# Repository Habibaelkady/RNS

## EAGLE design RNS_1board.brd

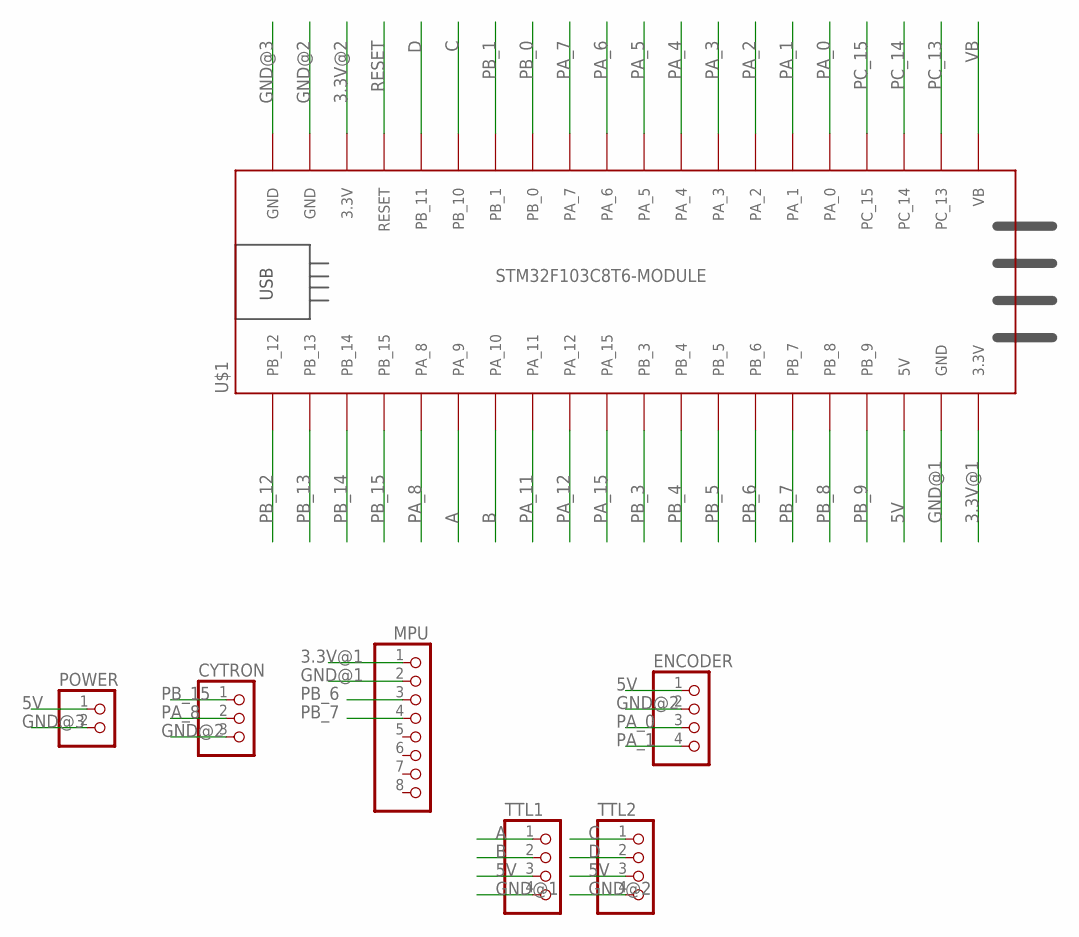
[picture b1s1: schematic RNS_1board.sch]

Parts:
CYTRON: PINHD-3_DATA; 1X03_DATA
ENCODER: PINHD-4_DATA; 1X04_DATA
MPU: PINHD-8_DATA; 1X08_DATA
POWER: PINHD-2_DATA; 1X02_DATA
TTL1, TTL2: PINHD-4_DATA; 1X04_DATA
U$1: STM32F103C8T6-MODULE

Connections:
3.3V@1: MPU.1, U$1.3.3V_1 (3.3V)
3.3V@2: U$1.3.3V_2 (3.3V)
5V: ENCODER.1, POWER.1, TTL1.3, TTL2.3, U$1.5V
A: TTL1.1, U$1.PA_9
B: TTL1.2, U$1.PA_10
C: TTL2.1, U$1.PB_10
D: TTL2.2, U$1.PB_11
GND@1: MPU.2, TTL1.4, U$1.GND_1 (GND)
GND@2: CYTRON.3, ENCODER.2, TTL2.4, U$1.GND_2 (GND)
GND@3: POWER.2, U$1.GND_3 (GND)
PA_0: ENCODER.3, U$1.PA_0
PA_1: ENCODER.4, U$1.PA_1
PA_2: U$1.PA_2
PA_3: U$1.PA_3
PA_4: U$1.PA_4
PA_5: U$1.PA_5
PA_6: U$1.PA_6
PA_7: U$1.PA_7
PA_8: CYTRON.2, U$1.PA_8
PA_11: U$1.PA_11
PA_12: U$1.PA_12
PA_15: U$1.PA_15
PB_0: U$1.PB_0
PB_1: U$1.PB_1
PB_3: U$1.PB_3
PB_4: U$1.PB_4
PB_5: U$1.PB_5
PB_6: MPU.3, U$1.PB_6
PB_7: MPU.4, U$1.PB_7
PB_8: U$1.PB_8
PB_9: U$1.PB_9
PB_12: U$1.PB_12
PB_13: U$1.PB_13
PB_14: U$1.PB_14
PB_15: CYTRON.1, U$1.PB_15
PC_13: U$1.PC_13
PC_14: U$1.PC_14
PC_15: U$1.PC_15
RESET: U$1.RESET
VB: U$1.VB

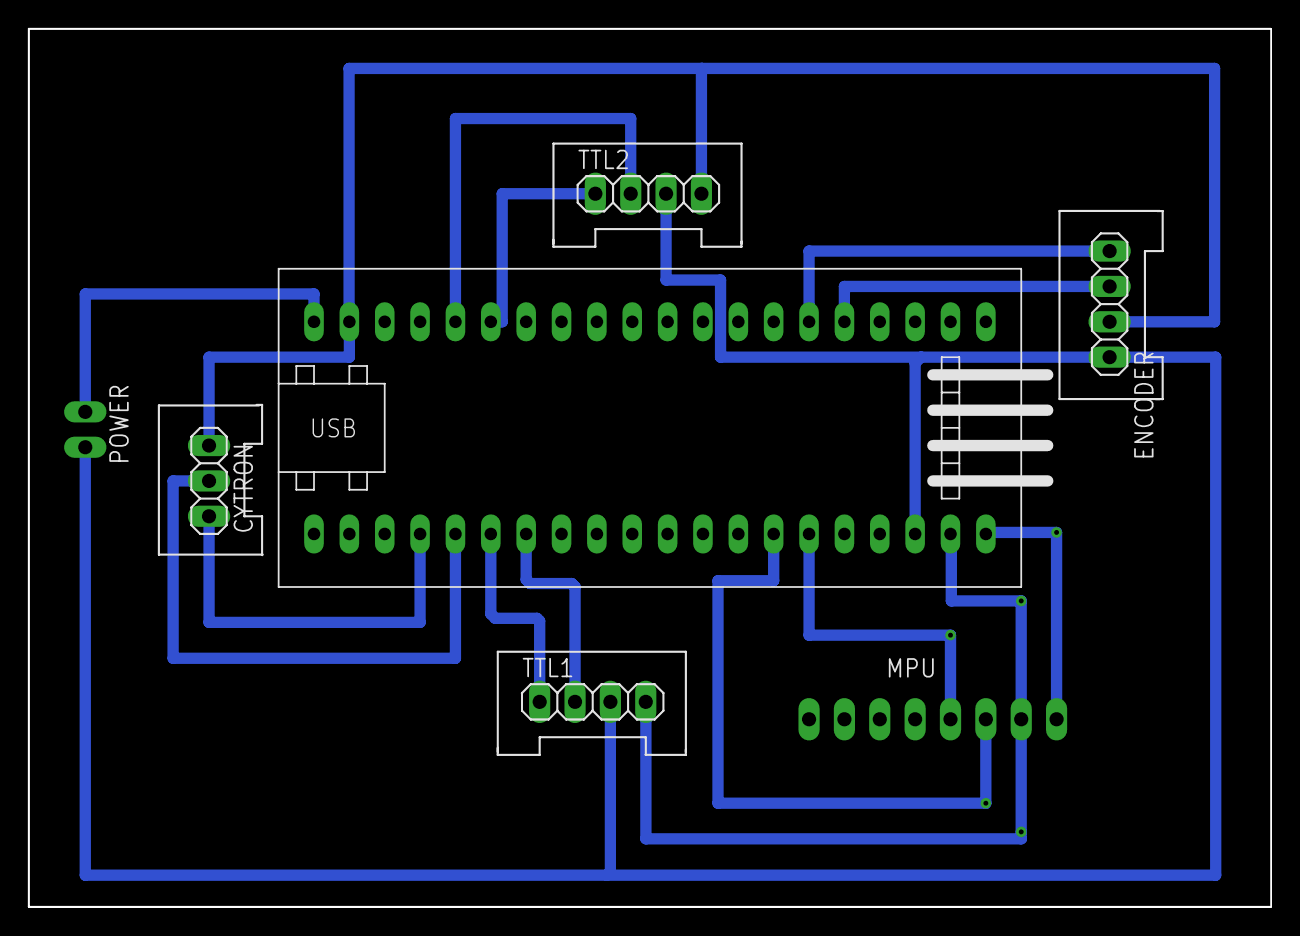
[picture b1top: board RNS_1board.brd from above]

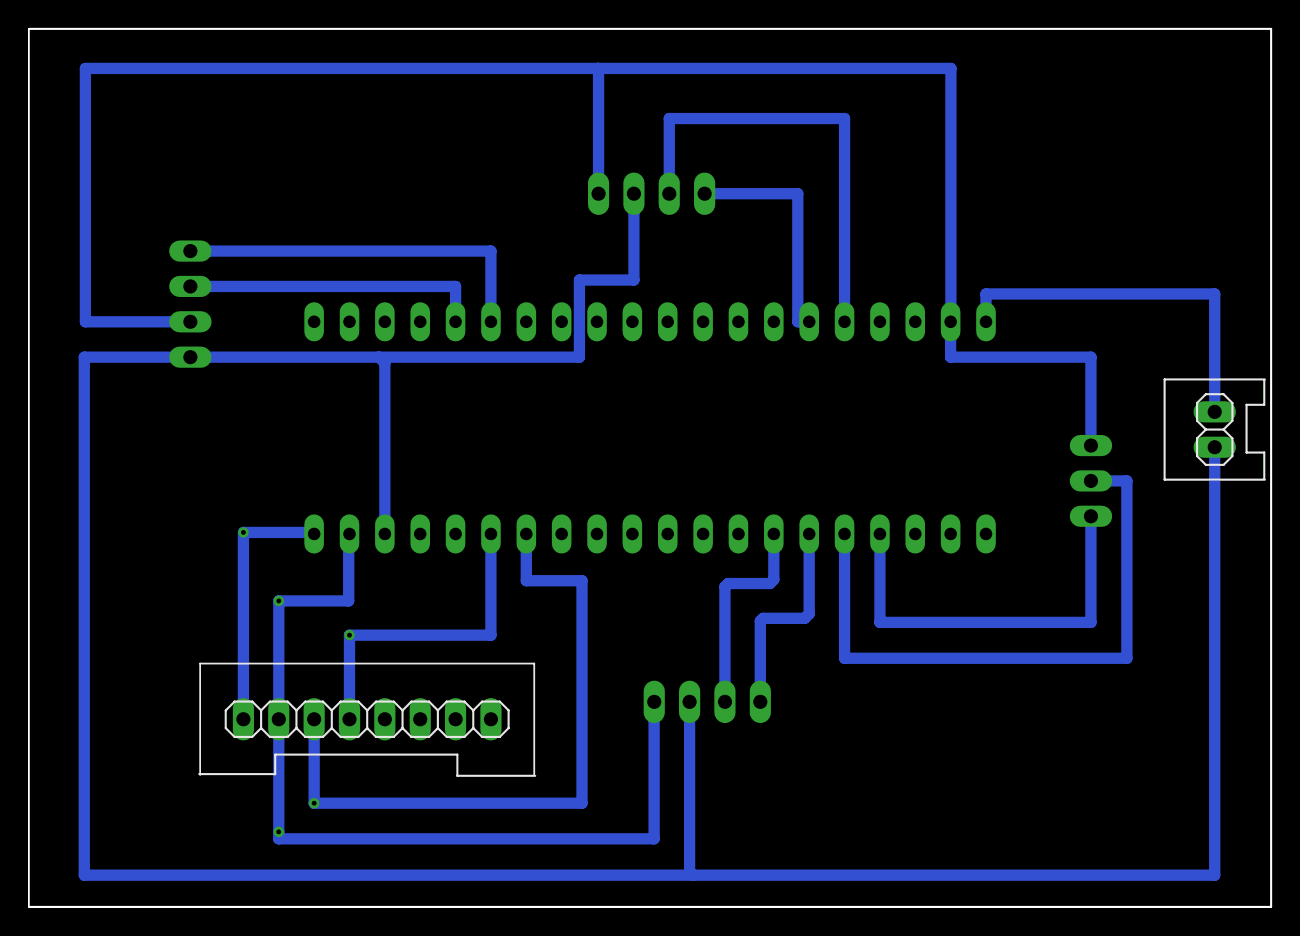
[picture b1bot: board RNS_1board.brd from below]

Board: 2 copper layers, 89.2 x 63.1 mm, 7 parts (2 on the bottom side), 15 nets.
